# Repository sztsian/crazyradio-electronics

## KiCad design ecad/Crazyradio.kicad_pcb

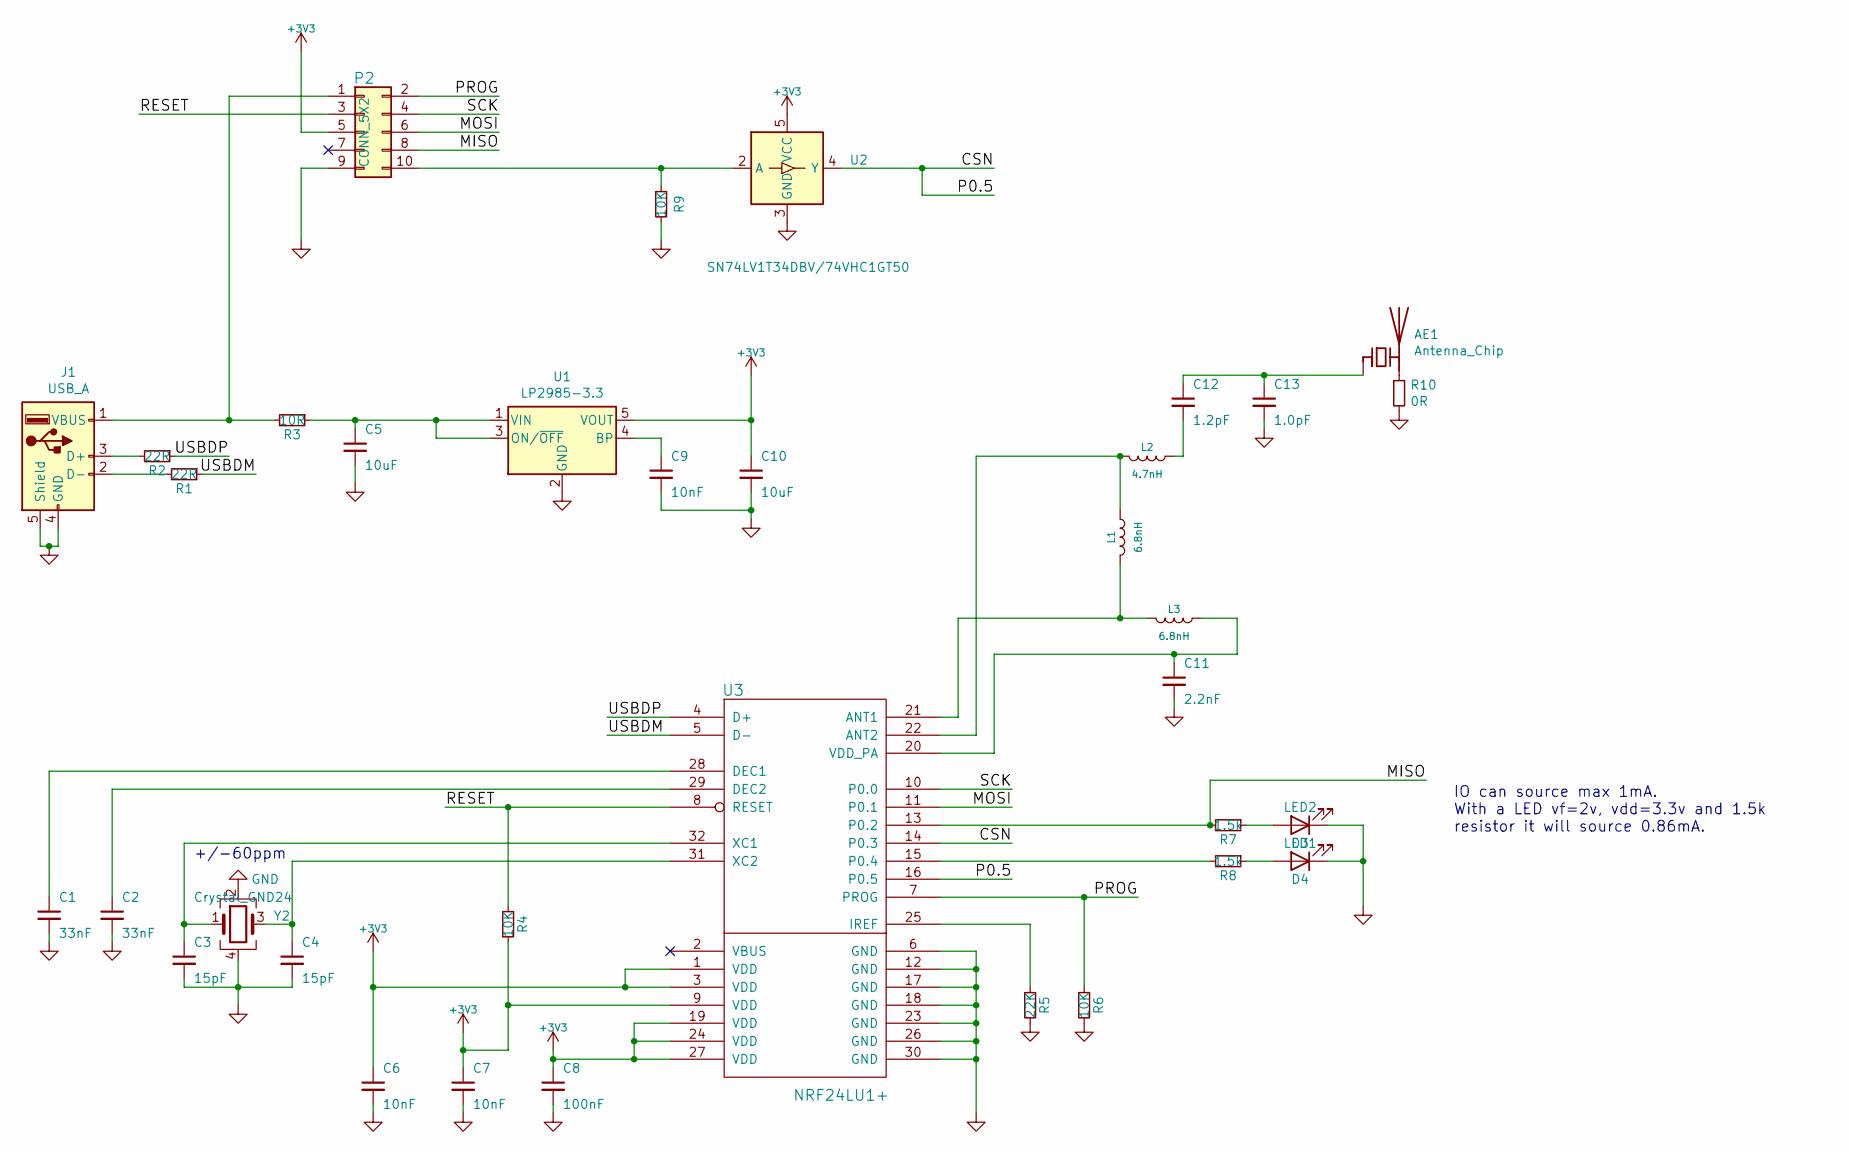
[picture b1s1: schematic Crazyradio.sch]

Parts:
AE1: Antenna_Chip; Texas_SWRA117D_2.4GHz_Right
C1, C2: 33nF; C_0603_1608Metric_Pad1.08x0.95mm_HandSolder
C3, C4: 15pF; C_0603_1608Metric_Pad1.08x0.95mm_HandSolder
C5, C10: 10uF; C_0603_1608Metric_Pad1.08x0.95mm_HandSolder
C6, C7, C9: 10nF; C_0603_1608Metric_Pad1.08x0.95mm_HandSolder
C8: 100nF; C_0603_1608Metric_Pad1.08x0.95mm_HandSolder
C11: 2.2nF; C_0603_1608Metric_Pad1.08x0.95mm_HandSolder
C12: 1.2pF; C_0603_1608Metric_Pad1.08x0.95mm_HandSolder
C13: 1.0pF; C_0603_1608Metric_Pad1.08x0.95mm_HandSolder
D3: LED2; LED_0603_1608Metric_Pad1.05x0.95mm_HandSolder
D4: LED1; LED_0603_1608Metric_Pad1.05x0.95mm_HandSolder
J1: USB_A
L1, L3: 6.8nH; L_0603_1608Metric_Pad1.05x0.95mm_HandSolder
L2: 4.7nH; L_0603_1608Metric_Pad1.05x0.95mm_HandSolder
P2: CONN_5X2; PinHeader_2x05_P2.54mm_Vertical
R1, R2: 22R; R_0603_1608Metric_Pad0.98x0.95mm_HandSolder
R3: 10R; R_0603_1608Metric_Pad0.98x0.95mm_HandSolder
R4, R6, R9: 10K; R_0603_1608Metric_Pad0.98x0.95mm_HandSolder
R5: 22K; R_0603_1608Metric_Pad0.98x0.95mm_HandSolder
R7, R8: 1.5k; R_0603_1608Metric_Pad0.98x0.95mm_HandSolder
R10: 0R; R_0603_1608Metric_Pad0.98x0.95mm_HandSolder
U1: LP2985-3.3; SOT-23-5
U2: SN74LV1T34DBV/74VHC1GT50; SOT-23-5
U3: NRF24LU1+; QFN-32-1EP_5x5mm_P0.5mm_EP3.3x3.3mm
Y2: Crystal_GND24; Crystal_SMD_2520-4Pin_2.5x2.0mm

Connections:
+3V3: C6.1, C7.1, C8.1, C10.1, P2.5, R4.2, U1.5 (VOUT), U2.5 (VCC), U3.1 (VDD), U3.3 (VDD), U3.9 (VDD), U3.19 (VDD), U3.24 (VDD), U3.27 (VDD)
/CSN: U2.4 (Y), U3.14 (P0.3), U3.16 (P0.5)
/MISO: P2.8, R7.2, U3.13 (P0.2)
/MOSI: P2.6, U3.11 (P0.1)
/PROG: P2.2, R6.1, U3.7 (PROG)
/RESET: P2.3, R4.1, U3.8 (RESET)
/SCK: P2.4, U3.10 (P0.0)
/USBDM: R1.1, U3.5 (D-)
/USBDP: R2.1, U3.4 (D+)
GND: C1.2, C2.2, C3.2, C4.2, C5.2, C6.2, C7.2, C8.2, C9.2, C10.2, C11.2, C13.2, D3.1 (K), D4.1 (K), J1.4 (GND), J1.5 (Shield), P2.9, R5.2, R6.2, R9.2, R10.2, U1.2 (GND), U2.3 (GND), U3.6 (GND), U3.12 (GND), U3.17 (GND), U3.18 (GND), U3.23 (GND), U3.26 (GND), U3.30 (GND), Y2.2, Y2.4
unnamed: AE1.1 (FEED), C12.1, C13.1
unnamed: AE1.2 (PCB_Trace), R10.1
unnamed: C1.1, U3.28 (DEC1)
unnamed: C2.1, U3.29 (DEC2)
unnamed: C3.1, U3.32 (XC1), Y2.1
unnamed: C4.1, U3.31 (XC2), Y2.3
unnamed: C5.1, R3.1, U1.1 (VIN), U1.3 (ON/~OFF~)
unnamed: C9.1, U1.4 (BP)
unnamed: C11.1, L3.1, U3.20 (VDD_PA)
unnamed: C12.2, L2.1
unnamed: D3.2 (A), R7.1
unnamed: D4.2 (A), R8.1
unnamed: J1.1 (VBUS), P2.1, R3.2
unnamed: J1.2 (D-), R1.2
unnamed: J1.3 (D+), R2.2
unnamed: L1.1, L2.2, U3.22 (ANT2)
unnamed: L1.2, L3.2, U3.21 (ANT1)
unnamed: P2.10, R9.1, U2.2 (A)
unnamed: R5.1, U3.25 (IREF)
unnamed: R8.2, U3.15 (P0.4)

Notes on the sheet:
IO can source max 1mA. With a LED vf=2v, vdd=3.3v and 1.5k resistor it will source 0.86mA.
+/-60ppm

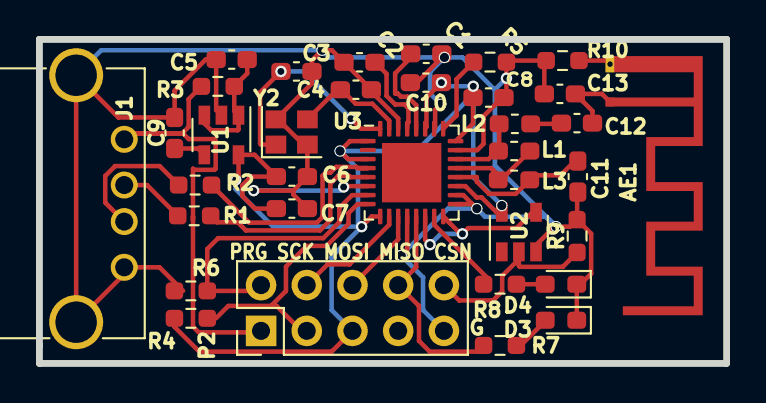
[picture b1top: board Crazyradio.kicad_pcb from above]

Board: 2 copper layers, 38.2 x 18.0 mm, 35 parts (0 on the bottom side), 30 nets.

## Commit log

2020-12-18 Rewrite using newer kicad and 0603 packages

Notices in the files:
ecad/Crazyradio.kicad_pcb:
Bitcraze AB (CC BY-NC-SA)
